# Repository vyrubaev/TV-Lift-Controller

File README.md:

# TVLift Controller

Профессиональная платформа управления лифтом для телевизора на базе ESP32.

Проект включает в себя:

- прошивку контроллера ESP32;
- мобильное приложение;
- сервер обновлений и управления;
- веб-панель администратора;
- аппаратную документацию;
- систему удаленного обновления прошивки (OTA — Over-the-Air);
- полную инженерную документацию.

---

# Основные возможности

- управление электроприводом лифта;
- поддержка Wi-Fi и Ethernet;
- первоначальная настройка через Captive Portal;
- безопасное удаленное обновление прошивки;
- хранение настроек во Flash памяти;
- REST API для мобильного приложения;
- журнал событий;
- диагностика устройства;
- поддержка нескольких аппаратных ревизий.

---

# Архитектура проекта

```
TVLift/

├── docs/               Документация
├── firmware/           Прошивка ESP32
├── backend/            Сервер
├── mobile/             Мобильное приложение
├── web-admin/          Панель администратора
├── hardware/           KiCad (схемы и PCB)
├── tools/              Скрипты и утилиты
├── component-library/  Библиотека компонентов
└── README.md
```

---

# Документация

## Архитектура

| Документ | Назначение |
|----------|------------|
| 00_ProjectVision.md | Цели проекта |
| 01_SystemArchitecture.md | Общая архитектура |
| 02_FirmwareArchitecture.md | Архитектура прошивки |
| 03_StateMachine.md | Конечный автомат |
| 04_API.md | REST API |
| 05_OTA.md | Система обновлений |

---

## Аппаратная часть

| Документ | Назначение |
|----------|------------|
| Board.md | Описание платы |
| Pinout.md | Назначение выводов |
| Power.md | Система питания |

---

## Библиотека компонентов

В проекте используется собственная библиотека утвержденных компонентов.

Все новые устройства должны использовать компоненты из этой библиотеки, если нет технической причины выбрать другой элемент.

---

# Используемые технологии

## Firmware

- ESP32
- ESP-IDF
- PlatformIO
- C++17

## Backend

- Python
- FastAPI
- PostgreSQL

## Mobile

- Flutter

## Web

- React
- TypeScript

---

# Основные принципы разработки

Проект строится по следующим правилам:

- модульная архитектура;
- минимальная связанность модулей;
- отсутствие глобальных переменных;
- отсутствие динамического выделения памяти в рабочем режиме;
- аппаратная независимость бизнес-логики;
- документирование всех архитектурных решений;
- обязательное код-ревью перед слиянием изменений.

---

# Структура прошивки

Firmware состоит из независимых модулей.

- Boot
- Configuration
- Storage
- Hardware Abstraction Layer (HAL)
- Network Manager
- OTA Manager
- REST API
- Elevator Controller
- Logger
- Diagnostics

---

# Состояния контроллера

Boot

↓

Hardware Init

↓

Load Configuration

↓

Network Connection

↓

Cloud Connection

↓

Ready

↓

Working

↓

Error Recovery

---

# Требования к качеству

- единый стиль кода;
- обязательное документирование публичных интерфейсов;
- отсутствие магических чисел;
- отсутствие дублирования кода;
- обязательные журналы ошибок;
- возможность безопасного восстановления после сбоя.

---

# Версионирование

Используется Semantic Versioning.

MAJOR.MINOR.PATCH

Например

2.4.15

---

# Лицензия

Определяется владельцем проекта.

---

# Статус проекта

🚧 В активной разработке.

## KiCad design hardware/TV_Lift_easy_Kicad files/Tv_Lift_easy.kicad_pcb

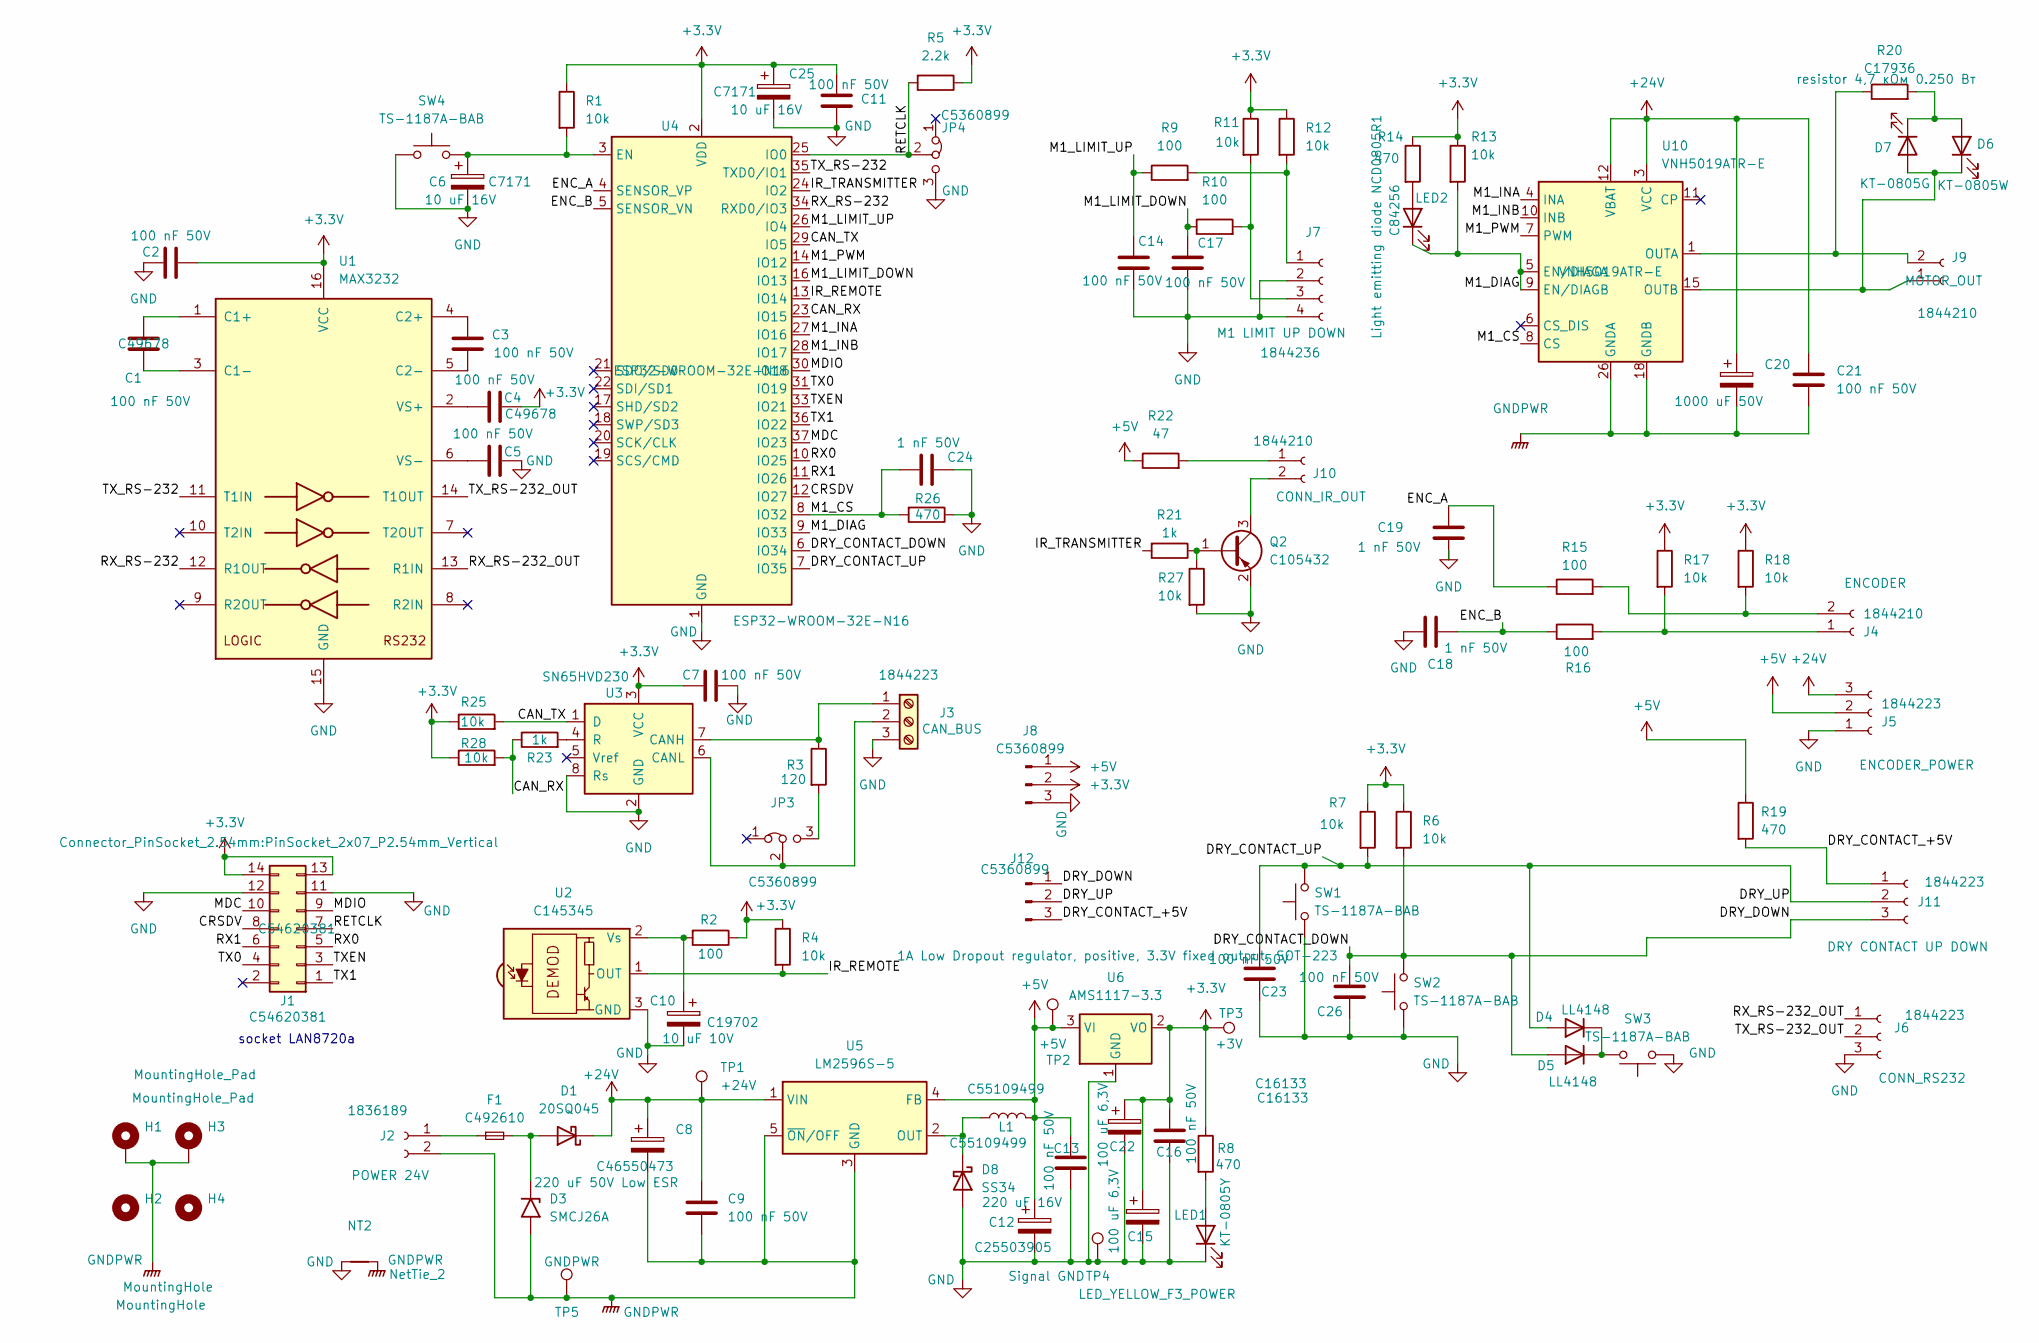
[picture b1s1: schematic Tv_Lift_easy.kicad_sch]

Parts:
C1, C2, C3, C4, C5, C7, C9, C11, C13, C14, C16, C17, C21, C23, C26: 100 nF 50V; C_0805_2012Metric
C6, C25: C7171; CP_EIA-3216-18_Kemet-A
C8: C46550473; CP_Elec_10x10
C10: C19702; C_0603_1608Metric
C12: C25503905; CP_Elec_6.3x7.7
C15, C22: C16133; CP_EIA-3528-21_Kemet-B_HandSolder
C18, C19, C24: 1 nF 50V; C_0805_2012Metric
C20: 1000 uF 50V; CP_Radial_D8.0mm_P3.50mm
D1: 20SQ045; D_DO-201AD_P15.24mm_Horizontal
D3: SMCJ26A; D_SMC
D4, D5: LL4148; D_MiniMELF
D6: KT-0805W; LED_0805_2012Metric
D7: KT-0805G; LED_0805_2012Metric
D8: SS34; D_SMA
F1: C492610; Fuseholder_XF-506P_mini_blade_C492610
H1, H3: MountingHole_Pad; MountingHole_2.7mm_M2.5_Pad_Via
H2, H4: MountingHole; MountingHole_2.7mm_M2.5_Pad_Via
J1: C54620381; PinSocket_2x07_P2.54mm_Vertical
J2: 1836189; PhoenixContact_MC_1,5_2-G-5.08_1x02_P5.08mm_Horizontal
J3, J5, J6, J11: 1844223; PhoenixContact_MC_1,5_3-G-3.5_1x03_P3.50mm_Horizontal
J4, J9, J10: 1844210; PhoenixContact_MC_1,5_2-G-3.5_1x02_P3.50mm_Horizontal
J7: 1844236; PhoenixContact_MC_1,5_4-G-3.5_1x04_P3.50mm_Horizontal
J8, J12: C5360899; PinHeader_1x03_P2.54mm_Vertical
JP3, JP4: C5360899; PinHeader_1x03_P2.54mm_Vertical
L1: C55109499; L_APV_ANR6045
LED1: KT-0805Y; LED_0805_2012Metric
LED2: C84256; LED_0805_2012Metric
NT2: NetTie_2; NetTie-2_THT_Pad1.0mm
Q2: C105432; SOT-23
R1, R4, R6, R7, R11, R12, R13, R17, R18, R25, R27, R28: 10k; R_0805_2012Metric
R2, R9, R10, R15, R16: 100; R_0805_2012Metric
R3: 120; R_0805_2012Metric
R5: 2.2k; R_0805_2012Metric
R8, R14, R19, R26: 470; R_0805_2012Metric
R20: C17936; R_1206_3216Metric
R21, R23: 1k; R_0805_2012Metric
R22: 47; R_1206_3216Metric
SW1, SW2, SW3, SW4: TS-1187A-BAB; SW_Push_1P1T_XKB_TS-1187A
TP1: +24V; TestPoint_Pad_D2.0mm
TP2: +5V; TestPoint_Pad_D2.0mm
TP3: +3V; TestPoint_Pad_D2.0mm
TP4: Signal GND; TestPoint_Pad_D2.0mm
TP5: GNDPWR; TestPoint_Pad_D2.0mm
U1: MAX3232; SOIC-16_3.9x9.9mm_P1.27mm
U2: C145345; Vishay_MOLD-3Pin
U3: SN65HVD230; SOIC-8_3.9x4.9mm_P1.27mm
U4: ESP32-WROOM-32E-N16; ESP32-WROOM-32
U5: LM2596S-5; TO-263-5_TabPin3
U6: AMS1117-3.3; SOT-223-3_TabPin2
U10: VNH5019ATR-E; ST_MultiPowerSO-30

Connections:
+3.3V: C2.2, C4.2, C7.1, C11.1, C15.1, C16.1, C22.1, C25.1, J1.13, J1.14, J8.2, R1.1, R2.1, R4.1, R5.1, R6.1, R7.1, R8.1, R11.1, R12.1, R13.1, R14.1, R17.1, R18.1, R25.1, R28.1, TP3.1 (1_1), U1.16 (VCC), U3.3 (VCC), U4.2 (VDD), U6.2 (VO)
+5V: C12.1, C13.1, J5.2, J8.1, L1.2, R19.1, R22.1, TP2.1 (1_1), U5.4 (FB), U6.3 (VI)
+24V: C8.1, C9.1, C20.1, C21.1, D1.1 (K), J5.3, TP1.1 (1_1), U5.1 (VIN), U10.3 (VCC), U10.12 (VBAT), U10.13 (VCC), U10.23 (VCC), U10.31 (VCC)
/CAN_RX: R23.1, R28.2, U4.23 (IO15)
/CAN_TX: R25.2, U3.1 (D), U4.29 (IO5)
/CRSDV: J1.8, U4.12 (IO27)
/DRY_CONTACT_+5V: J11.1, J12.3, R19.2
/DRY_CONTACT_DOWN: C26.1, D5.2 (A), J11.3, J12.1, R6.2, SW2.2, U4.6 (IO34)
/DRY_CONTACT_UP: C23.1, D4.2 (A), J11.2, J12.2, R7.2, SW1.2, U4.7 (IO35)
/ENC_A: C19.1, R15.1, U4.4 (SENSOR_VP)
/ENC_B: C18.2, R16.1, U4.5 (SENSOR_VN)
/IR_REMOTE: R4.2, U2.1 (OUT), U4.13 (IO14)
/IR_TRANSMITTER: R21.2, U4.24 (IO2)
/M1_CS: C24.2, R26.2, U4.8 (IO32), U10.8 (CS)
/M1_DIAG: LED2.1 (K), R13.2, U4.9 (IO33), U10.5 (EN/DIAGA), U10.9 (EN/DIAGB)
/M1_INA: U4.27 (IO16), U10.4 (INA)
/M1_INB: U4.28 (IO17), U10.10 (INB)
/M1_LIMIT_DOWN: C17.1, R10.1, U4.16 (IO13)
/M1_LIMIT_UP: C14.1, R9.1, U4.26 (IO4)
/M1_PWM: U4.14 (IO12), U10.7 (PWM)
/MDC: J1.10, U4.37 (IO23)
/MDIO: J1.9, U4.30 (IO18)
/RETCLK: J1.7, JP4.2 (C), R5.2, U4.25 (IO0)
/RX0: J1.5, U4.10 (IO25)
/RX1: J1.6, U4.11 (IO26)
/RX_RS-232: U1.12 (R1OUT), U4.34 (RXD0/IO3)
/RX_RS-232_OUT: J6.1, U1.13 (R1IN)
/TX0: J1.4, U4.31 (IO19)
/TX1: J1.1, U4.36 (IO22)
/TXEN: J1.3, U4.33 (IO21)
/TX_RS-232: U1.11 (T1IN), U4.35 (TXD0/IO1)
/TX_RS-232_OUT: J6.2, U1.14 (T1OUT)
GND: C2.1, C5.2, C6.2, C7.2, C10.2, C11.2, C12.2, C13.2, C14.2, C15.2, C16.2, C17.2, C18.1, C19.2, C22.2, C23.2, C24.1, C25.2, C26.2, D8.2 (A), J1.11, J1.12, J3.3, J5.1, J6.3, J7.2, J7.4, J8.3, JP4.3 (B), LED1.1 (K), NT2.1, Q2.2 (E), R26.1, R27.2, SW1.1, SW2.1, SW3.1, SW4.1, TP4.1 (1_1), U1.15 (GND), U2.3 (GND), U3.2 (GND), U3.8 (Rs), U4.1 (GND), U4.15 (GND), U4.38 (GND), U4.39 (GND), U6.1 (GND)
GNDPWR: C8.2, C9.2, C20.2, C21.2, D3.2 (A2), H1.1 (1_1), H3.1 (1_1), J2.2, NT2.2, TP5.1 (1_1), U5.3 (GND), U5.5 (~ON/OFF), U10.18 (GNDB), U10.19 (GNDB), U10.20 (GNDB), U10.26 (GNDA), U10.27 (GNDA), U10.28 (GNDA)
unnamed: D1.2 (A), D3.1 (A1), F1.2
unnamed: D4.1 (K), D5.1 (K), SW3.2
unnamed: D6.2 (A), D7.1 (K), R20.2
unnamed: D6.1 (K), D7.2 (A), J9.1 (M+), U10.15 (OUTB), U10.16 (OUTB), U10.21 (OUTB), U10.32 (OUTB)
unnamed: D8.1 (K), L1.1, U5.2 (OUT)
unnamed: F1.1, J2.1
unnamed: J3.1, R3.1, U3.7 (CANH)
unnamed: J3.2, JP3.2 (C), U3.6 (CANL)
unnamed: J4.1, R16.2, R17.2
unnamed: J4.2, R15.2, R18.2
unnamed: J7.1, R9.2, R12.2
unnamed: J7.3, R10.2, R11.2
unnamed: J9.2 (M-), R20.1, U10.1 (OUTA), U10.25 (OUTA), U10.30 (OUTA), U10.33 (OUTA)
unnamed: J10.1, R22.2
unnamed: J10.2, Q2.3 (C)
unnamed: JP3.3 (B), R3.2
unnamed: LED1.2 (A), R8.2
unnamed: LED2.2 (A), R14.2
unnamed: Q2.1 (B), R21.1, R27.1
unnamed: C1.1, U1.1 (C1+)
unnamed: C1.2, U1.3 (C1-)
unnamed: C3.1, U1.4 (C2+)
unnamed: C3.2, U1.5 (C2-)
unnamed: C4.1, U1.2 (VS+)
unnamed: C5.1, U1.6 (VS-)
unnamed: C10.1, R2.2, U2.2 (Vs)
unnamed: R23.2, U3.4 (R)
unnamed: C6.1, R1.2, SW4.2, U4.3 (EN)

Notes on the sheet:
socket LAN8720a

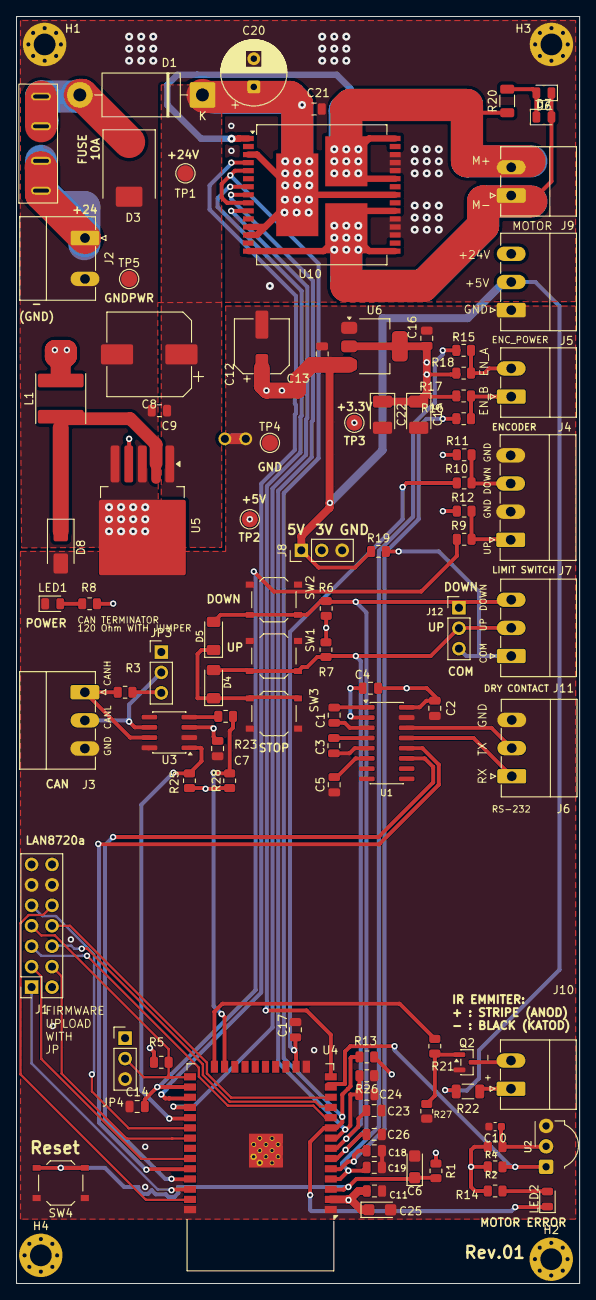
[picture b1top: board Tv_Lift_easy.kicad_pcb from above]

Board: 4 copper layers, 70.0 x 157.5 mm, 100 parts (0 on the bottom side), 62 nets.

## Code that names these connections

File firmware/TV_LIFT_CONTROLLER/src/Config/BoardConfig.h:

#pragma once

#include <stdint.h>

namespace BoardConfig
{
    // Board name and revision
    constexpr char BOARD_NAME[] = "TV Lift Controller";
    constexpr char BOARD_REVISION[] = "REV_A";

    // Частота процессора ESP32
    constexpr uint32_t CPU_FREQUENCY_MHZ = 240;

    // -------------------------
    // Motor 1
    // -------------------------

    constexpr uint8_t MOTOR1_INA = 16;
    constexpr uint8_t MOTOR1_INB = 17;
    constexpr uint8_t MOTOR1_PWM= 12; // WARNING - This pin is used by the ESP32 for bootstrapping. Using it may cause issues during boot.
    constexpr uint8_t MOTOR1_DIAG = 33; // пин DIAG с драйвера мотора, который сигнализирует о неисправности драйвера
    constexpr uint8_t MOTOR1_CURR_SENS = 32; //пин для измерения тока мотора с выхода драйвера мотора

    constexpr uint8_t MOTOR_DEFAULT_SPEED = 180; // range 0-255
    

    // -------------------------
    // ENCODERS
    // -------------------------

    constexpr uint8_t ENC_A = 36; // Physical pin 4 of ESP32-WROOM-32D
    constexpr uint8_t ENC_B = 39; // Physical pin 5 of ESP32-WROOM-32D


    // -------------------------
    // Dry contacts
    // -------------------------

    constexpr uint8_t DRY_CONTACT_DOWN_PIN = 34; 
    constexpr uint8_t DRY_CONTACT_UP_PIN = 35;

    // -------------------------
    // Limit switches
    // -------------------------

    constexpr uint8_t LIMIT_SWITCH_DOWN_PIN = 13;
    constexpr uint8_t LIMIT_SWITCH_UP_PIN = 4;

    // -------------------------
    // Communication
    // -------------------------

    constexpr uint8_t UART_TX_PIN = 1;
    constexpr uint8_t UART_RX_PIN = 3;

    constexpr uint8_t CAN_TX_PIN = 5; // WARNING - This pin is used by the ESP32 for bootstrapping. Using it may cause issues during boot.
    constexpr uint8_t CAN_RX_PIN = 15; // WARNING - This pin is used by the ESP32 for bootstrapping. Using it may cause issues during boot.

    constexpr uint8_t IR_RECEIVER_PIN = 14;
    constexpr uint8_t IR_TRANSMITTER_PIN = 2;

    // -------------------------
    // Ethernet
    // -------------------------

    constexpr uint8_t ETH_RETCLK = 0;
    constexpr uint8_t ETH_MDC = 23;
    constexpr uint8_t ETH_MDIO = 18;
    constexpr uint8_t ETH_RX1 = 26;
    constexpr uint8_t ETH_TX1 = 22;
    constexpr uint8_t ETH_CRS_DV = 27;
    constexpr uint8_t ETH_TX_EN = 21;
    constexpr uint8_t ETH_RX0 = 25;
    constexpr uint8_t ETH_TX0 = 19;

}
